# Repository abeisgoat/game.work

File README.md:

# Game.work Files

Keep in mind, this project has many rough edges so this build will require some effort.

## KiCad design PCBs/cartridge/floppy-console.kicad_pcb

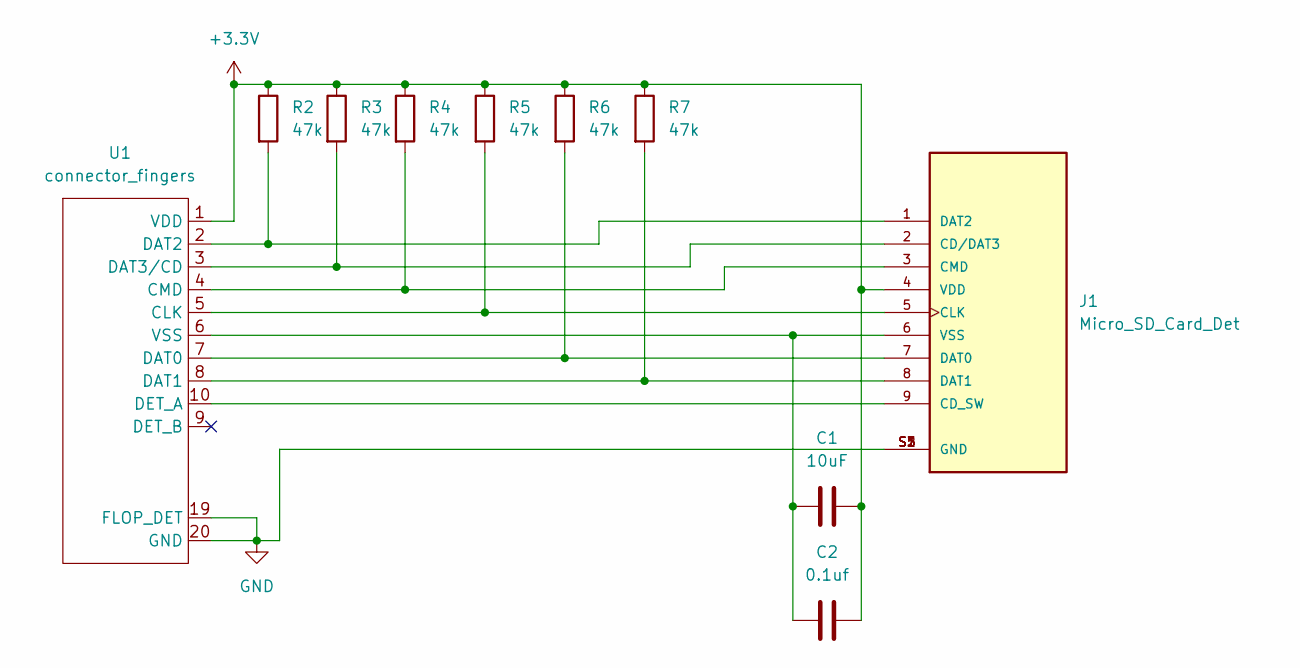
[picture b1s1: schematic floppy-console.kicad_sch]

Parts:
C1: 10uF; C_0603_1608Metric
C2: 0.1uf; C_0402_1005Metric
J1: Micro_SD_Card_Det; HRS_DM3CS-SF; PARTREV n/a
R2, R3, R4, R5, R6, R7: 47k; R_0402_1005Metric
U1: connector_fingers; FLOPPY_CART_EDGE

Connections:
+3V3: C1.2, C2.2, J1.4 (VDD), R2.1, R3.1, R4.1, R5.1, R6.1, R7.1, U1.1 (VDD)
GND: J1.S1 (GND), J1.S2 (GND), J1.S3 (GND), J1.S5 (GND), U1.19 (FLOP_DET), U1.20 (GND)
unnamed: C1.1, C2.1, J1.6 (VSS), U1.6 (VSS)
unnamed: J1.9 (CD_SW), U1.10 (DET_A)
unnamed: J1.1 (DAT2), R2.2, U1.2 (DAT2)
unnamed: J1.2 (CD/DAT3), R3.2, U1.3 (DAT3/CD)
unnamed: J1.3 (CMD), R4.2, U1.4 (CMD)
unnamed: J1.5 (CLK), R5.2, U1.5 (CLK)
unnamed: J1.7 (DAT0), R6.2, U1.7 (DAT0)
unnamed: J1.8 (DAT1), R7.2, U1.8 (DAT1)

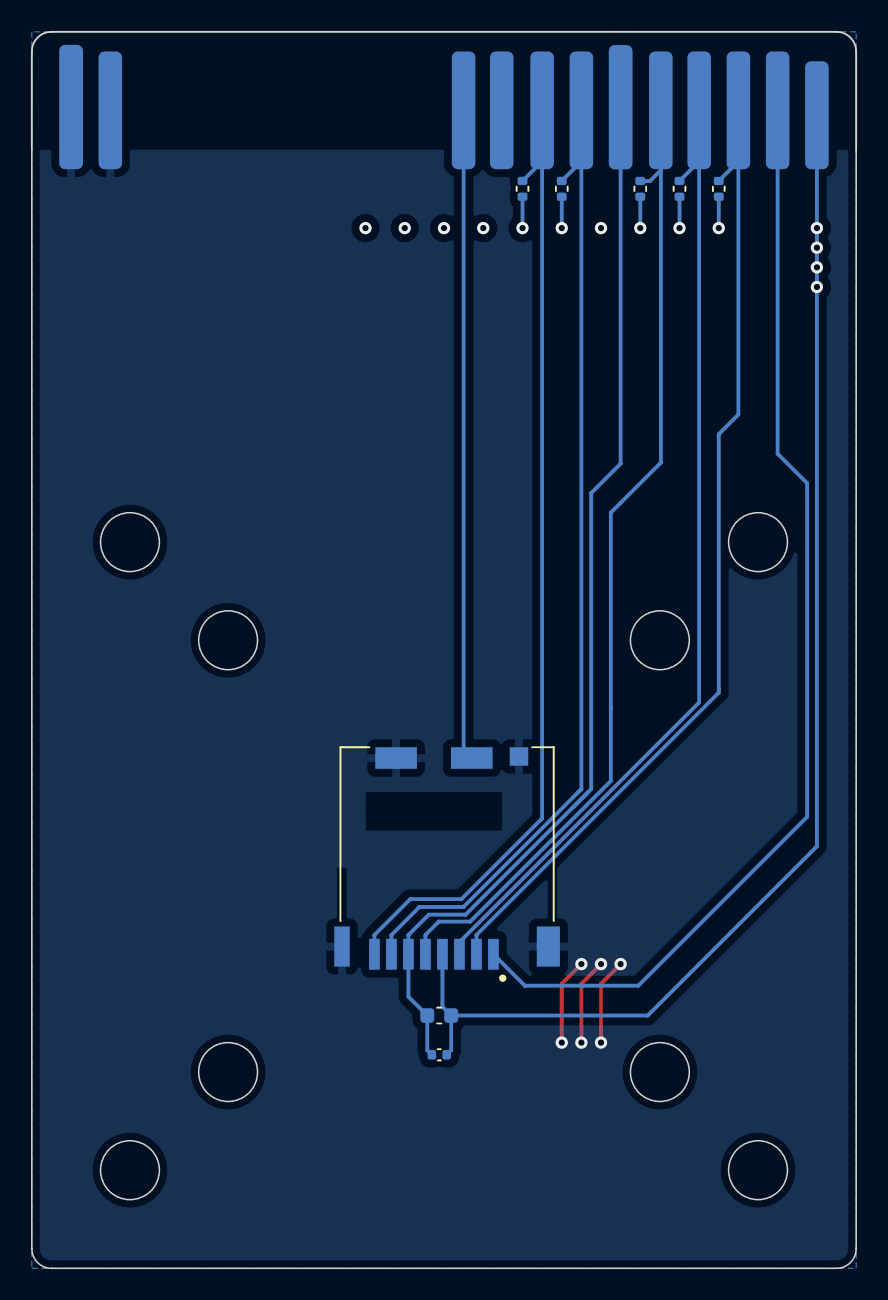
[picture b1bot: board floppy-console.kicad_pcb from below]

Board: 2 copper layers, 53.3 x 80.0 mm, 9 parts (8 on the bottom side), 10 nets.

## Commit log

2023-07-10 Adds PCBs
2023-07-10 Remove weird Tinkercad link
